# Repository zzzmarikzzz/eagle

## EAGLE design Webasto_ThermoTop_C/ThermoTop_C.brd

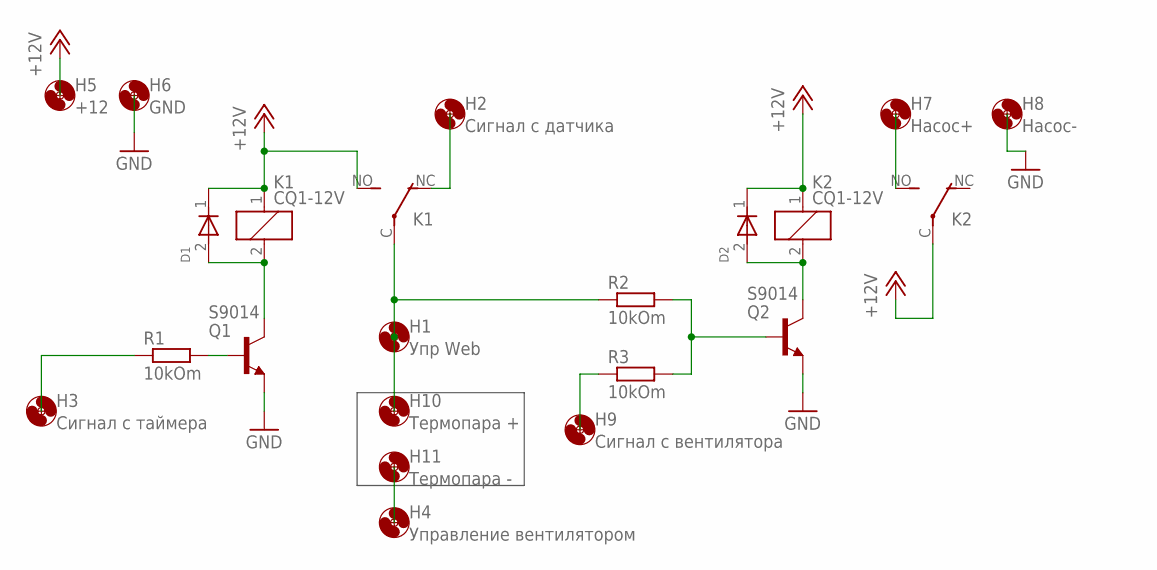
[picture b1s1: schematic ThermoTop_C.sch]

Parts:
D1, D2: DIODE; SOD80
H1: Упр Web; 2,8
H2: Сигнал с датчика; 2,8
H3: Сигнал с таймера; 2,8
H4: Управление вентилятором; 2,8
H5: +12; 3,0
H6: GND; 3,0
H7: Насос+; 3,0
H8: Насос-; 3,0
H9: Сигнал с вентилятора; 2,8
H10: Термопара +; 2,8
H11: Термопара -; 2,8
K1, K2: CQ1-12V; CQ1
Q1, Q2: S9014; TO92
R1, R2, R3: 10kOm; R0603

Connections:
+12V: D1.1 (KATOD), D2.1 (KATOD), H5.P$1, K1.1, K1.NO (S), K2.1, K2.C
GND: H6.P$1, H8.P$1, Q1.3 (E), Q2.3 (E)
unnamed: D1.2 (ANOD), K1.2, Q1.1 (C)
unnamed: Q1.2 (B), R1.2
unnamed: H3.P$1, R1.1
unnamed: H1.P$1, H10.P$1, K1.C, R2.1
unnamed: H4.P$1, H11.P$1
unnamed: H2.P$1, K1.NC (O)
unnamed: H7.P$1, K2.NO (S)
unnamed: Q2.2 (B), R2.2, R3.2
unnamed: D2.2 (ANOD), K2.2, Q2.1 (C)
unnamed: H9.P$1, R3.1

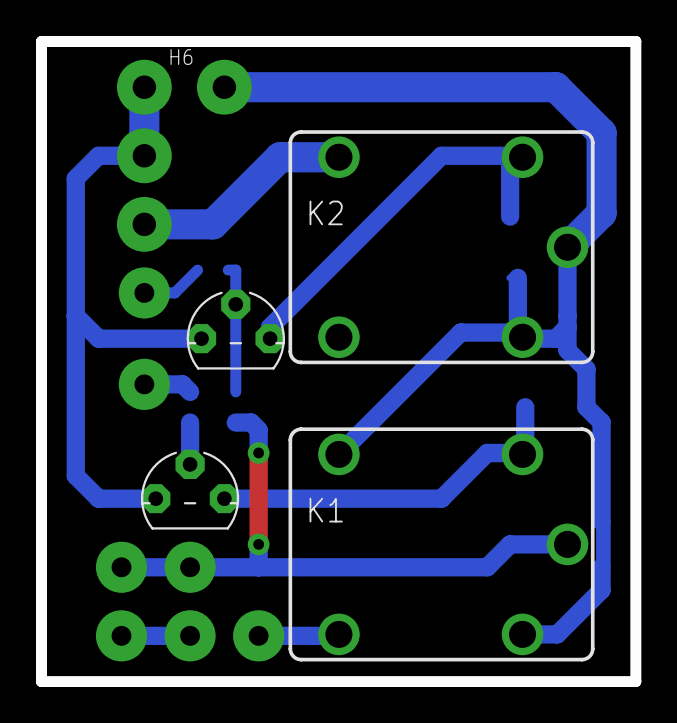
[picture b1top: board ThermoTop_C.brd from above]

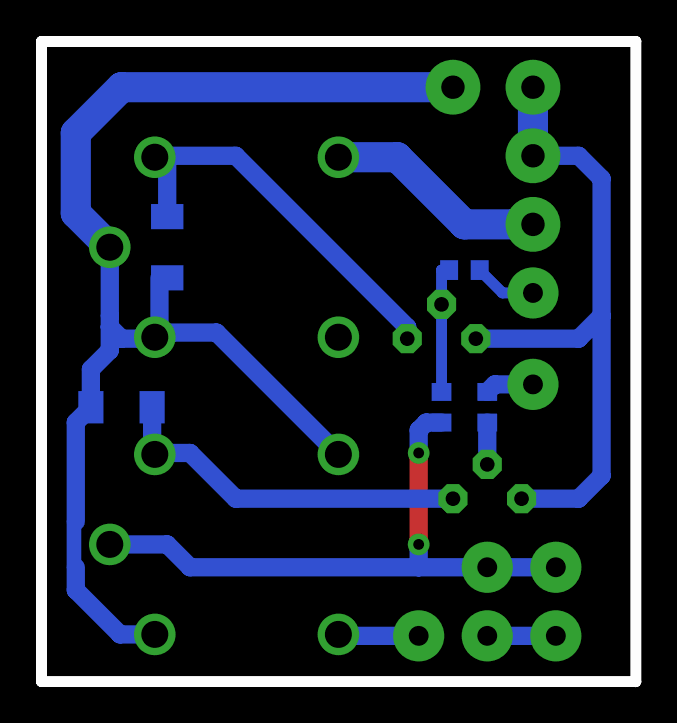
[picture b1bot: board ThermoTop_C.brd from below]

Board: 2 copper layers, 33.0 x 35.6 mm, 20 parts (5 on the bottom side), 12 nets.

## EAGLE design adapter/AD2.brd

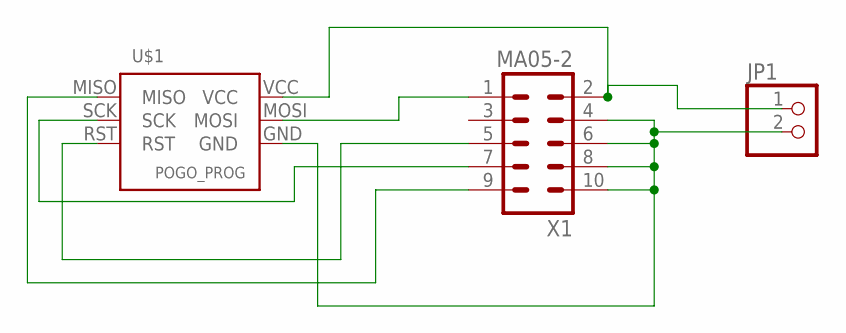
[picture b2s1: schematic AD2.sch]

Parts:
JP1: PINHD-1X2/90; 1X02/90
U$1: POGO_PROG
X1: MA05-2

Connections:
unnamed: U$1.MOSI, X1.1
unnamed: U$1.RST, X1.5
unnamed: U$1.SCK, X1.7
unnamed: U$1.MISO, X1.9
unnamed: JP1.1, U$1.VCC, X1.2
unnamed: JP1.2, U$1.GND, X1.4, X1.6, X1.8, X1.10

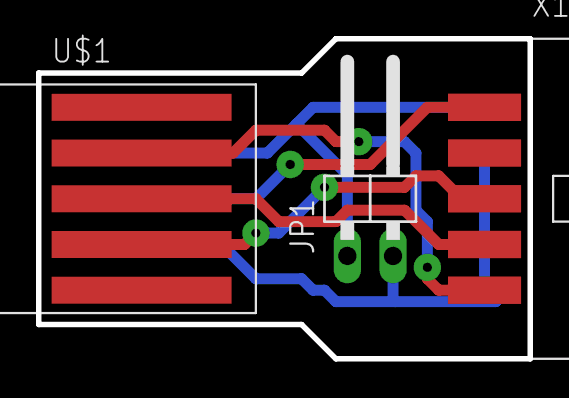
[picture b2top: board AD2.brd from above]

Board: 2 copper layers, 27.3 x 17.8 mm, 3 parts (0 on the bottom side), 6 nets.

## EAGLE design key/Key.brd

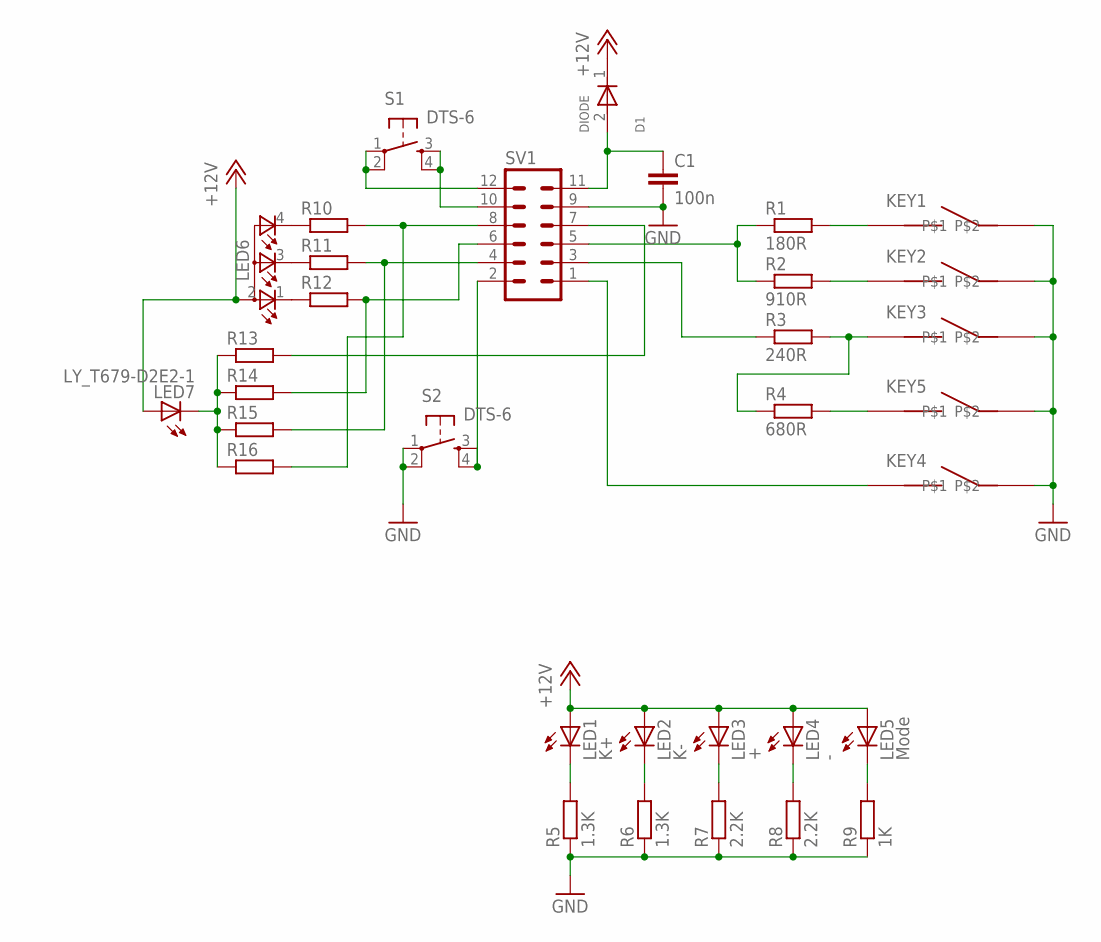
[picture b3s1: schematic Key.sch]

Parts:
C1: 100n; C0805K
D1: DIODE; SOD80
KEY1, KEY2, KEY3, KEY4, KEY5: PRINT_KEYPRINTED-KEY; PRINT_KEY
LED1: K+; PLCC2
LED2: K-; PLCC2
LED3: +; PLCC2
LED4: -; PLCC2
LED5: Mode; PLCC2
LED6: TOPLED-3; P-LCC-4-3
LED7: LY_T679-D2E2-1; PLCC2
R1: 180R; R1206
R2: 910R; R1206
R3: 240R; R1206
R4: 680R; R1206
R5, R6: 1.3K; R1206
R7, R8: 2.2K; R1206
R9: 1K; R1206
R10, R11, R12, R13, R14, R15, R16: R-EU_R0603; R0603
S1, S2: DTS-6
SV1: MA06-2

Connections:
+12V: D1.1 (KATOD), LED1.A, LED2.A, LED3.A, LED4.A, LED5.A, LED6.2 (A2), LED7.A
GND: C1.2, KEY1.P$2, KEY2.P$2, KEY3.P$2, KEY4.P$2, KEY5.P$2, R5.1, R6.1, R7.1, R8.1, R9.1, S2.1, S2.2, SV1.9
unnamed: C1.1, D1.2 (ANOD), SV1.11
unnamed: R1.1, R2.1, SV1.5
unnamed: KEY1.P$1, R1.2
unnamed: KEY2.P$1, R2.2
unnamed: R3.1, SV1.3
unnamed: KEY3.P$1, R3.2, R4.1
unnamed: LED1.C, R5.2
unnamed: KEY5.P$1, R4.2
unnamed: KEY4.P$1, SV1.1
unnamed: LED2.C, R6.2
unnamed: LED3.C, R7.2
unnamed: LED4.C, R8.2
unnamed: LED5.C, R9.2
unnamed: S2.3, S2.4, SV1.2
unnamed: LED6.4 (CGREEN), R10.1
unnamed: LED6.3 (CBLUE), R11.1
unnamed: LED6.1 (CRED), R12.1
unnamed: R11.2, R15.2, SV1.4
unnamed: R12.2, R14.2, SV1.6
unnamed: R10.2, R16.2, SV1.8
unnamed: S1.3, S1.4, SV1.10
unnamed: S1.1, S1.2, SV1.12
unnamed: LED7.C, R13.1, R14.1, R15.1, R16.1
unnamed: R13.2, SV1.7

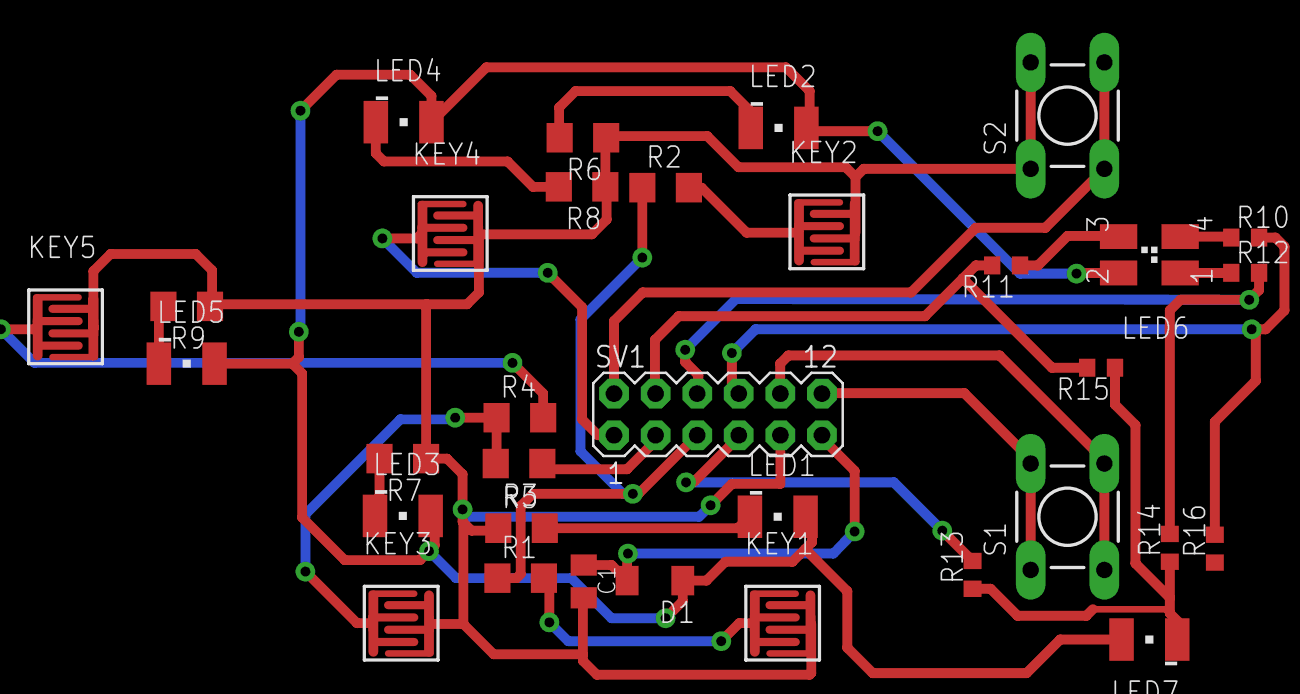
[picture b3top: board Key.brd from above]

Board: 2 copper layers, 33 parts (0 on the bottom side), 26 nets.
